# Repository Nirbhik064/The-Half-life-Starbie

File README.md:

# The-Half-life-Starbie
Starbie is designed to sit on your desk, show its personality on a small display, and react to how you handle it. Tilting, moving, and otherwise checking in on your pet are meant to be part of the experience.

The board includes a microcontroller, display, motion sensor, and environmental sensor in a compact PCB design. It is USB powered and built around beginner-friendly through-hole soldering for the add-on components.

This repo is here because, truthfully, I was a bit late regarding submission for week 1, and was travelling throughout week 2. I have already made them both, I just couldn't journal them s I had to put it in as a Tier 1 project.

Here is the schematics of the project;

And here is the PCB of the project;

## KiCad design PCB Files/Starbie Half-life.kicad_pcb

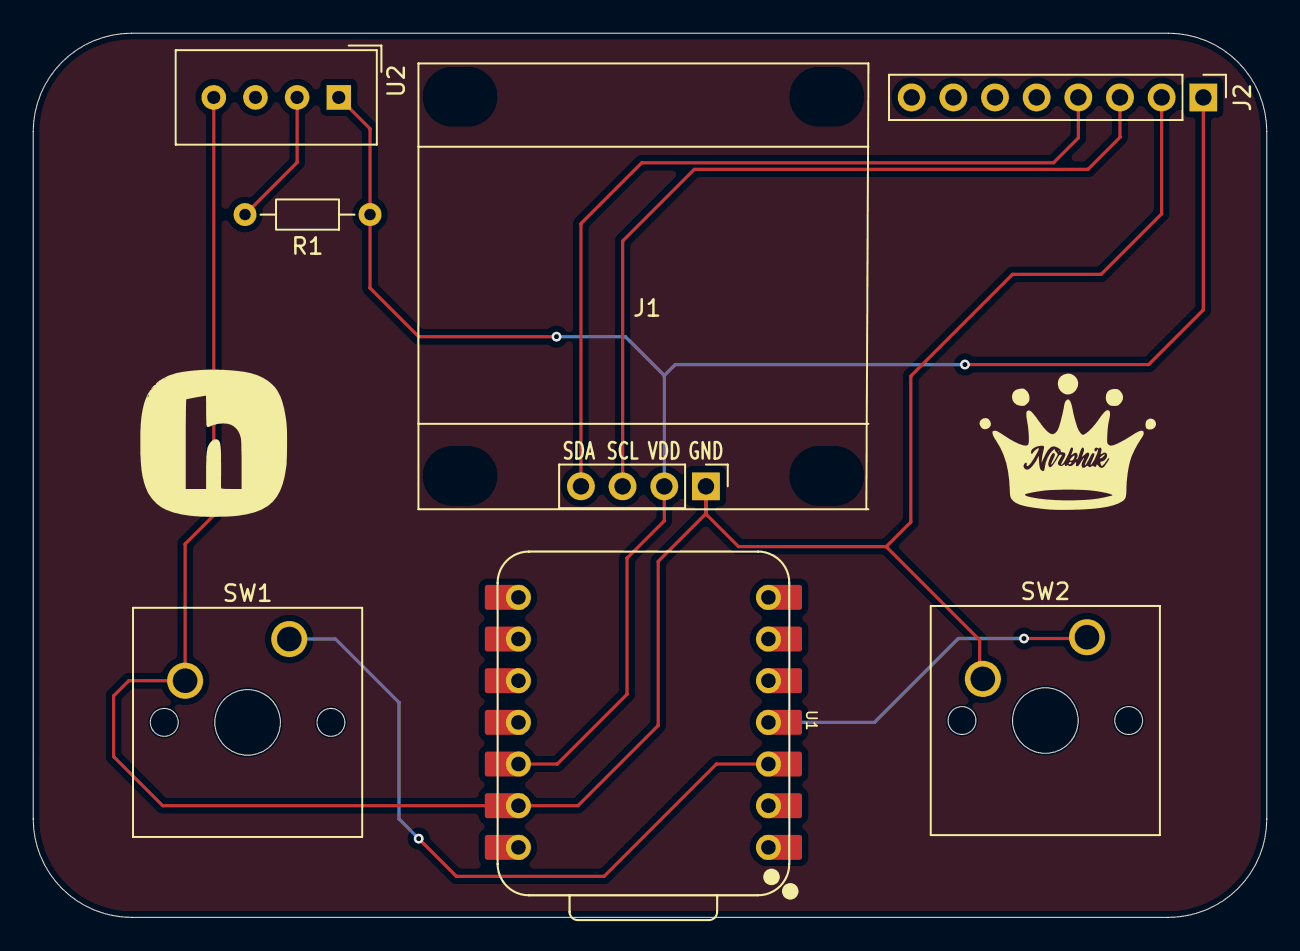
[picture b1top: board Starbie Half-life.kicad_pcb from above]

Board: 2 copper layers, 75.2 x 53.9 mm, 7 parts (0 on the bottom side), 7 nets.

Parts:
J1: Conn_01x04_Pin; Display_128x64_096_I2C
J2: Conn_01x08_Pin; PinHeader_1x08_P2.54mm_Vertical
R1: 10k; R_Axial_DIN0204_L3.6mm_D1.6mm_P7.62mm_Horizontal
SW1, SW2: SW_Push; SW_Cherry_MX_1.00u_PCB
U1: XIAO-ESP32-C3-SMD; XIAO-ESP32-C6-DIP
U2: DHT11; Aosong_DHT11_5.5x12.0_P2.54mm

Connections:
+3.3V: J1.2 (Pin_3), J2.1, R1.1, U1.12 (3V3_OUT), U2.1 (VDD)
DHT11 DATA: R1.2, U2.2 (DATA)
GND: J1.1 (Pin_4), J2.2, SW1.2, SW2.2, U1.13 (GND), U2.4 (GND)
GPIO2: SW1.1, U1.3 (D2)
GPIO3: SW2.1, U1.4 (D3)
SCL: J1.3 (Pin_2), J2.3
SDA: J1.4 (Pin_1), J2.4
